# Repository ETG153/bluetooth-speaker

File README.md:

# Bluetooth-speaker
Wireless bluetooth speaker with high quality sound.

## Features
- Custom made sound card with an ESP32 and a high quality 24bit 192khz dac, Hi-Fi quality
- Completely wireless: battery charging and BMS included
- Amplifiers and crossover custom made for this product, design is power efficient
- Can support LDAC bluetooth codec for higher music bitrate (up to 990 kbps)

## Documentation
- Schematics can be found in the hardware folder
- Code is self explanatory, thus no documentation is needed
- PlatformIO: https://platformio.org/
- DAC datasheet: https://statics.cirrus.com/pubs/proDatasheet/CS4344-45-48_F2.pdf
- ESP32 datasheet: https://www.espressif.com/sites/default/files/documentation/esp32-wroom-32e_esp32-wroom-32ue_datasheet_en.pdf
- Bluetooth library used: https://github.com/pschatzmann/ESP32-A2DP

- Oamk documentation in its own folder

## Architecture

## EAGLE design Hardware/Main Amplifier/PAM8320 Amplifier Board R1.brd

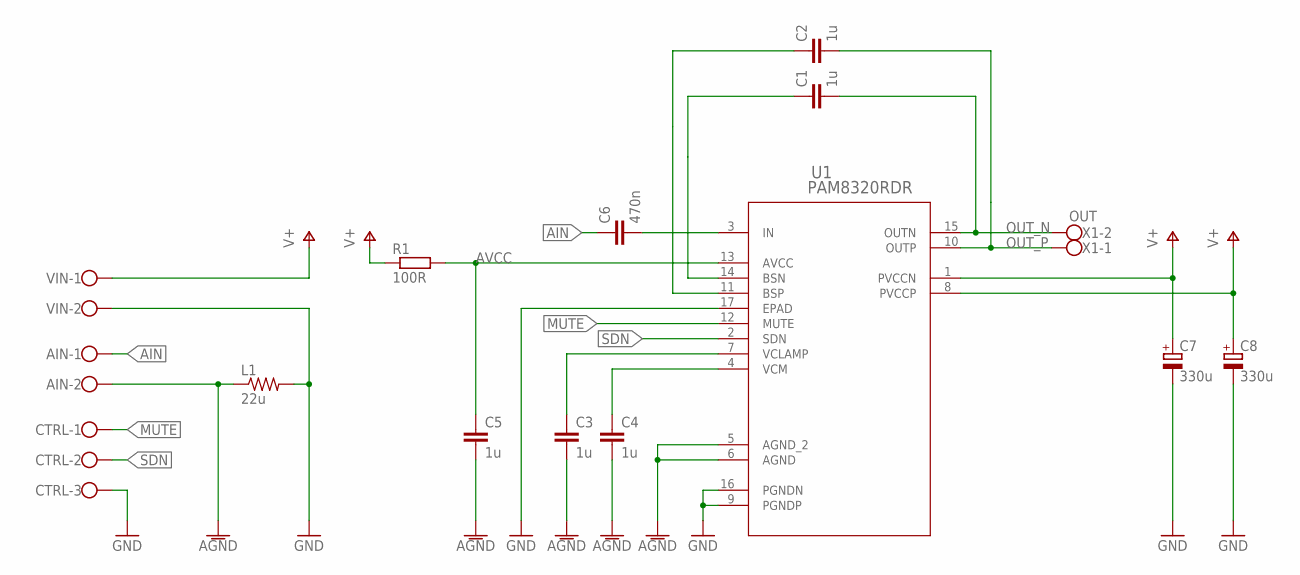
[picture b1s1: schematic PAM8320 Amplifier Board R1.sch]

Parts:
AIN: W237-102
C1, C2, C3, C4, C5: 1u; C1206
C6: 470n; C1206
C7, C8: 330u; E3,5-8
CTRL: W237-103
L1: 22u; R0805
R1: 100R; R0603
U1: PAM8320RDR; SO-16EP_3P9X9P9_DIO
VIN: W237-102
X1: OUT; W237-102

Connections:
AGND: AIN.2, C3.2, C4.2, C5.2, L1.1, U1.5 (AGND_2), U1.6 (AGND)
AIN: AIN.1, C6.1
AVCC: C5.1, R1.2, U1.13 (AVCC)
BSN: C1.1, U1.14 (BSN)
BSP: C2.1, U1.11 (BSP)
GND: C7.-, C8.-, CTRL.3, L1.2, U1.9 (PGNDP), U1.16 (PGNDN), U1.17 (EPAD), VIN.2
MUTE: CTRL.1, U1.12 (MUTE)
unnamed: C3.1, U1.7 (VCLAMP)
unnamed: C4.1, U1.4 (VCM)
unnamed: C6.2, U1.3 (IN)
OUT_N: C1.2, U1.15 (OUTN), X1.2
OUT_P: C2.2, U1.10 (OUTP), X1.1
SDN: CTRL.2, U1.2 (SDN)
V+: C7.+, C8.+, R1.1, U1.1 (PVCCN), U1.8 (PVCCP), VIN.1

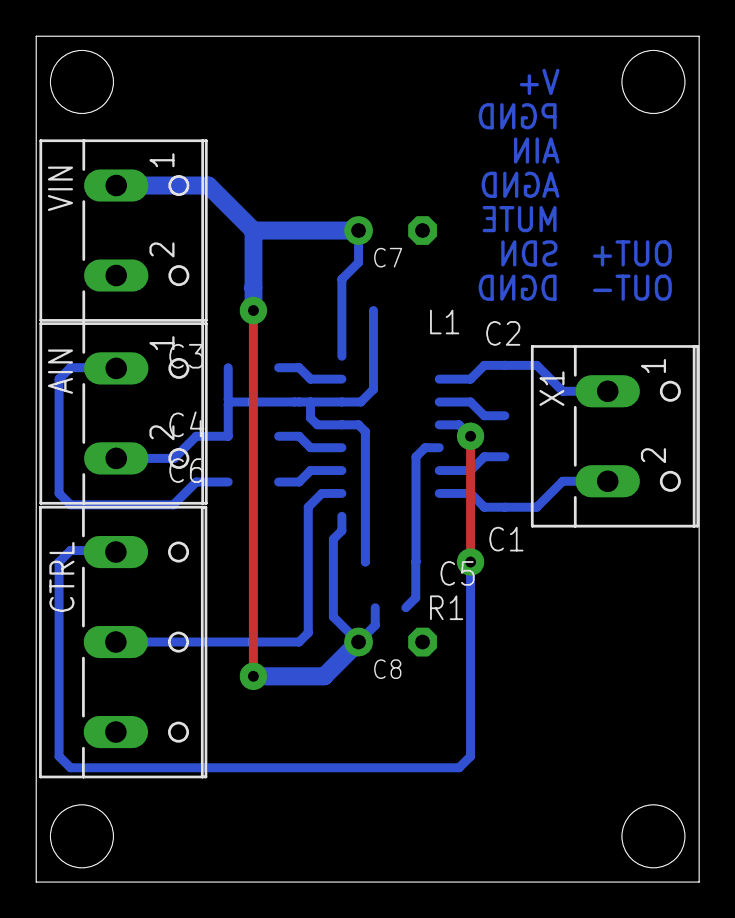
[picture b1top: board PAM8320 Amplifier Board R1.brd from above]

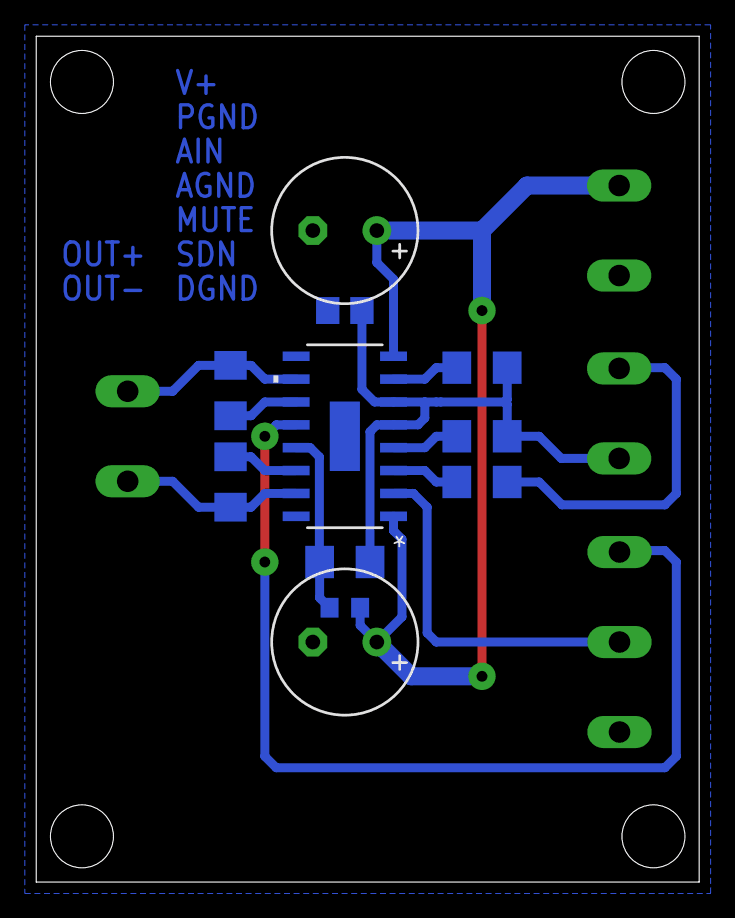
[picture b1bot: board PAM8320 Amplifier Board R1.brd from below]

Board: 2 copper layers, 36.8 x 47.0 mm, 15 parts (11 on the bottom side), 14 nets.

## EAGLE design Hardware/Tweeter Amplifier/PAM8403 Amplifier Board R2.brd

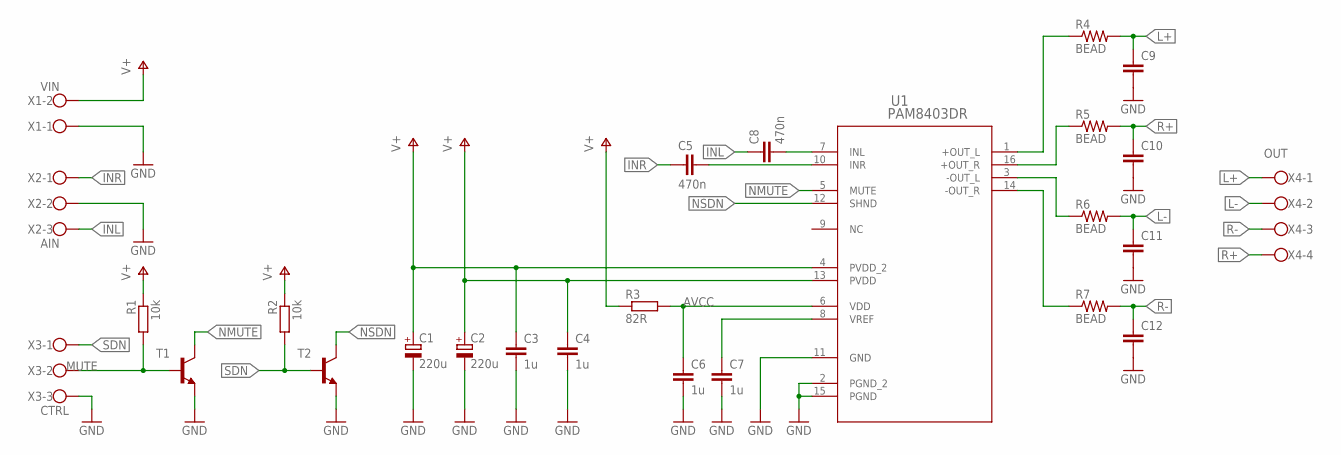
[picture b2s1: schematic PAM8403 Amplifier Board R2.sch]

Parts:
C1, C2: 220u; UD-10X10_NICHICON
C3, C4, C6, C7: 1u; C0805
C5, C8: 470n; C1206
C9, C10, C11, C12: C-EUC0603; C0603
R1, R2: 10k; R0603
R3: 82R; R1206
R4, R5, R6, R7: BEAD; R0805
T1, T2: MMBT3904LT1-NPN-SOT23-BEC; SOT23-BEC
U1: PAM8403DR; SOIC_8403DR_DIO
X1: VIN; W237-102
X2: AIN; W237-103
X3: CTRL; W237-103
X4: OUT; W237-4

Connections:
AVCC: C6.1, R3.2, U1.6 (VDD)
GND: C1.-, C2.-, C3.2, C4.2, C6.2, C7.2, C9.2, C10.2, C11.2, C12.2, T1.E, T2.E, U1.2 (PGND_2), U1.11 (GND), U1.15 (PGND), X1.1, X2.2, X3.3
INL: C8.1, X2.3
INR: C5.1, X2.1
L: C8.2, U1.7 (INL)
L+: C9.1, R4.2, X4.1
L-: C11.1, R6.2, X4.2
MUTE: R1.2, T1.B, X3.2
unnamed: R5.1, U1.16 (+OUT_R)
unnamed: R6.1, U1.3 (-OUT_L)
unnamed: R4.1, U1.1 (+OUT_L)
unnamed: R7.1, U1.14 (-OUT_R)
NMUTE: T1.C, U1.5 (MUTE)
NSDN: T2.C, U1.12 (SHND)
R: C5.2, U1.10 (INR)
R+: C10.1, R5.2, X4.4
R-: C12.1, R7.2, X4.3
SDN: R2.2, T2.B, X3.1
V+: C1.+, C2.+, C3.1, C4.1, R1.1, R2.1, R3.1, U1.4 (PVDD_2), U1.13 (PVDD), X1.2
VREF: C7.1, U1.8 (VREF)

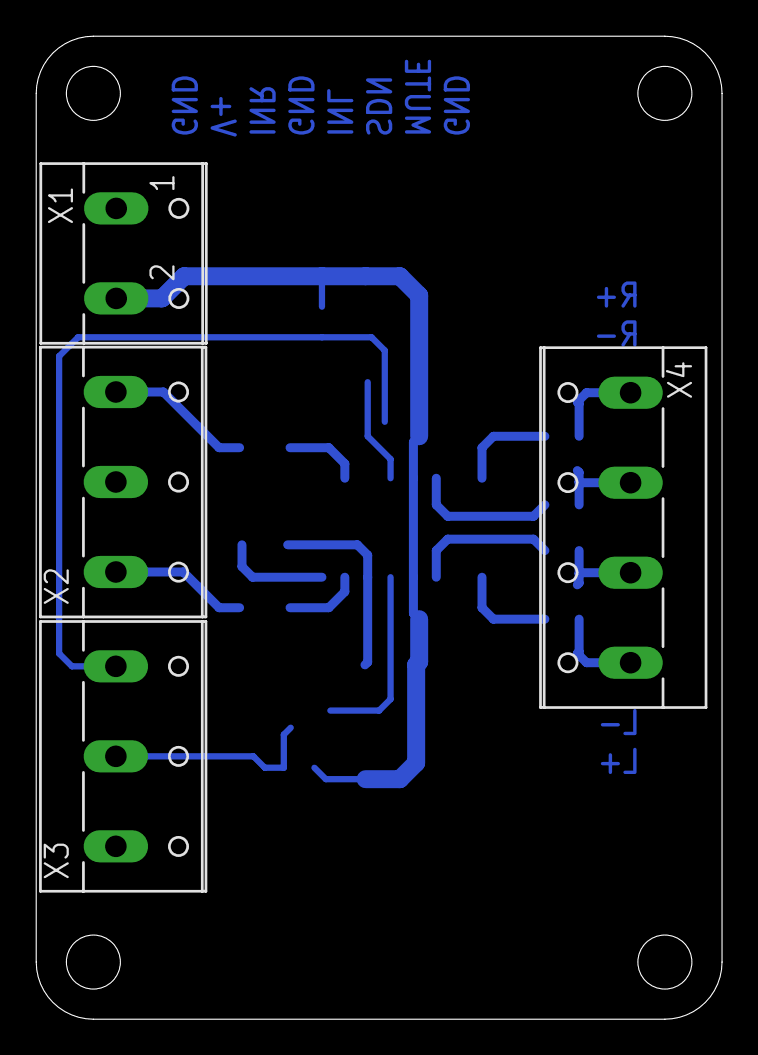
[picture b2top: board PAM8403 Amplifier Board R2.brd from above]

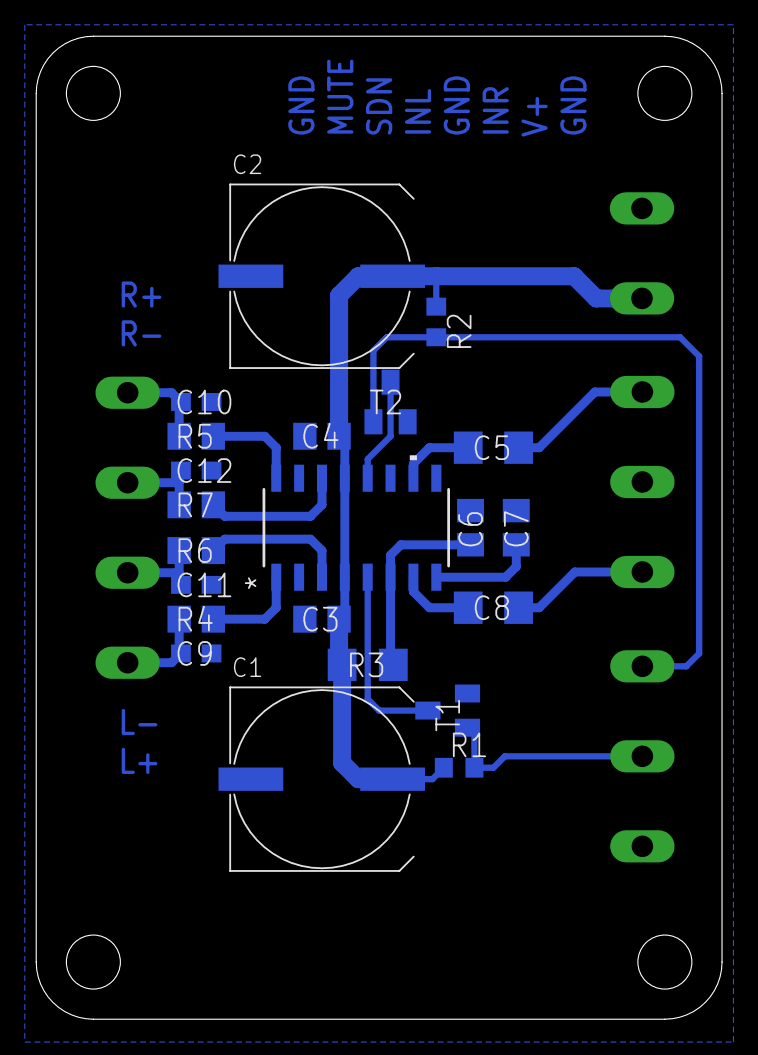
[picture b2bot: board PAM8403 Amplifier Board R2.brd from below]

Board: 2 copper layers, 38.1 x 54.6 mm, 26 parts (22 on the bottom side), 20 nets.

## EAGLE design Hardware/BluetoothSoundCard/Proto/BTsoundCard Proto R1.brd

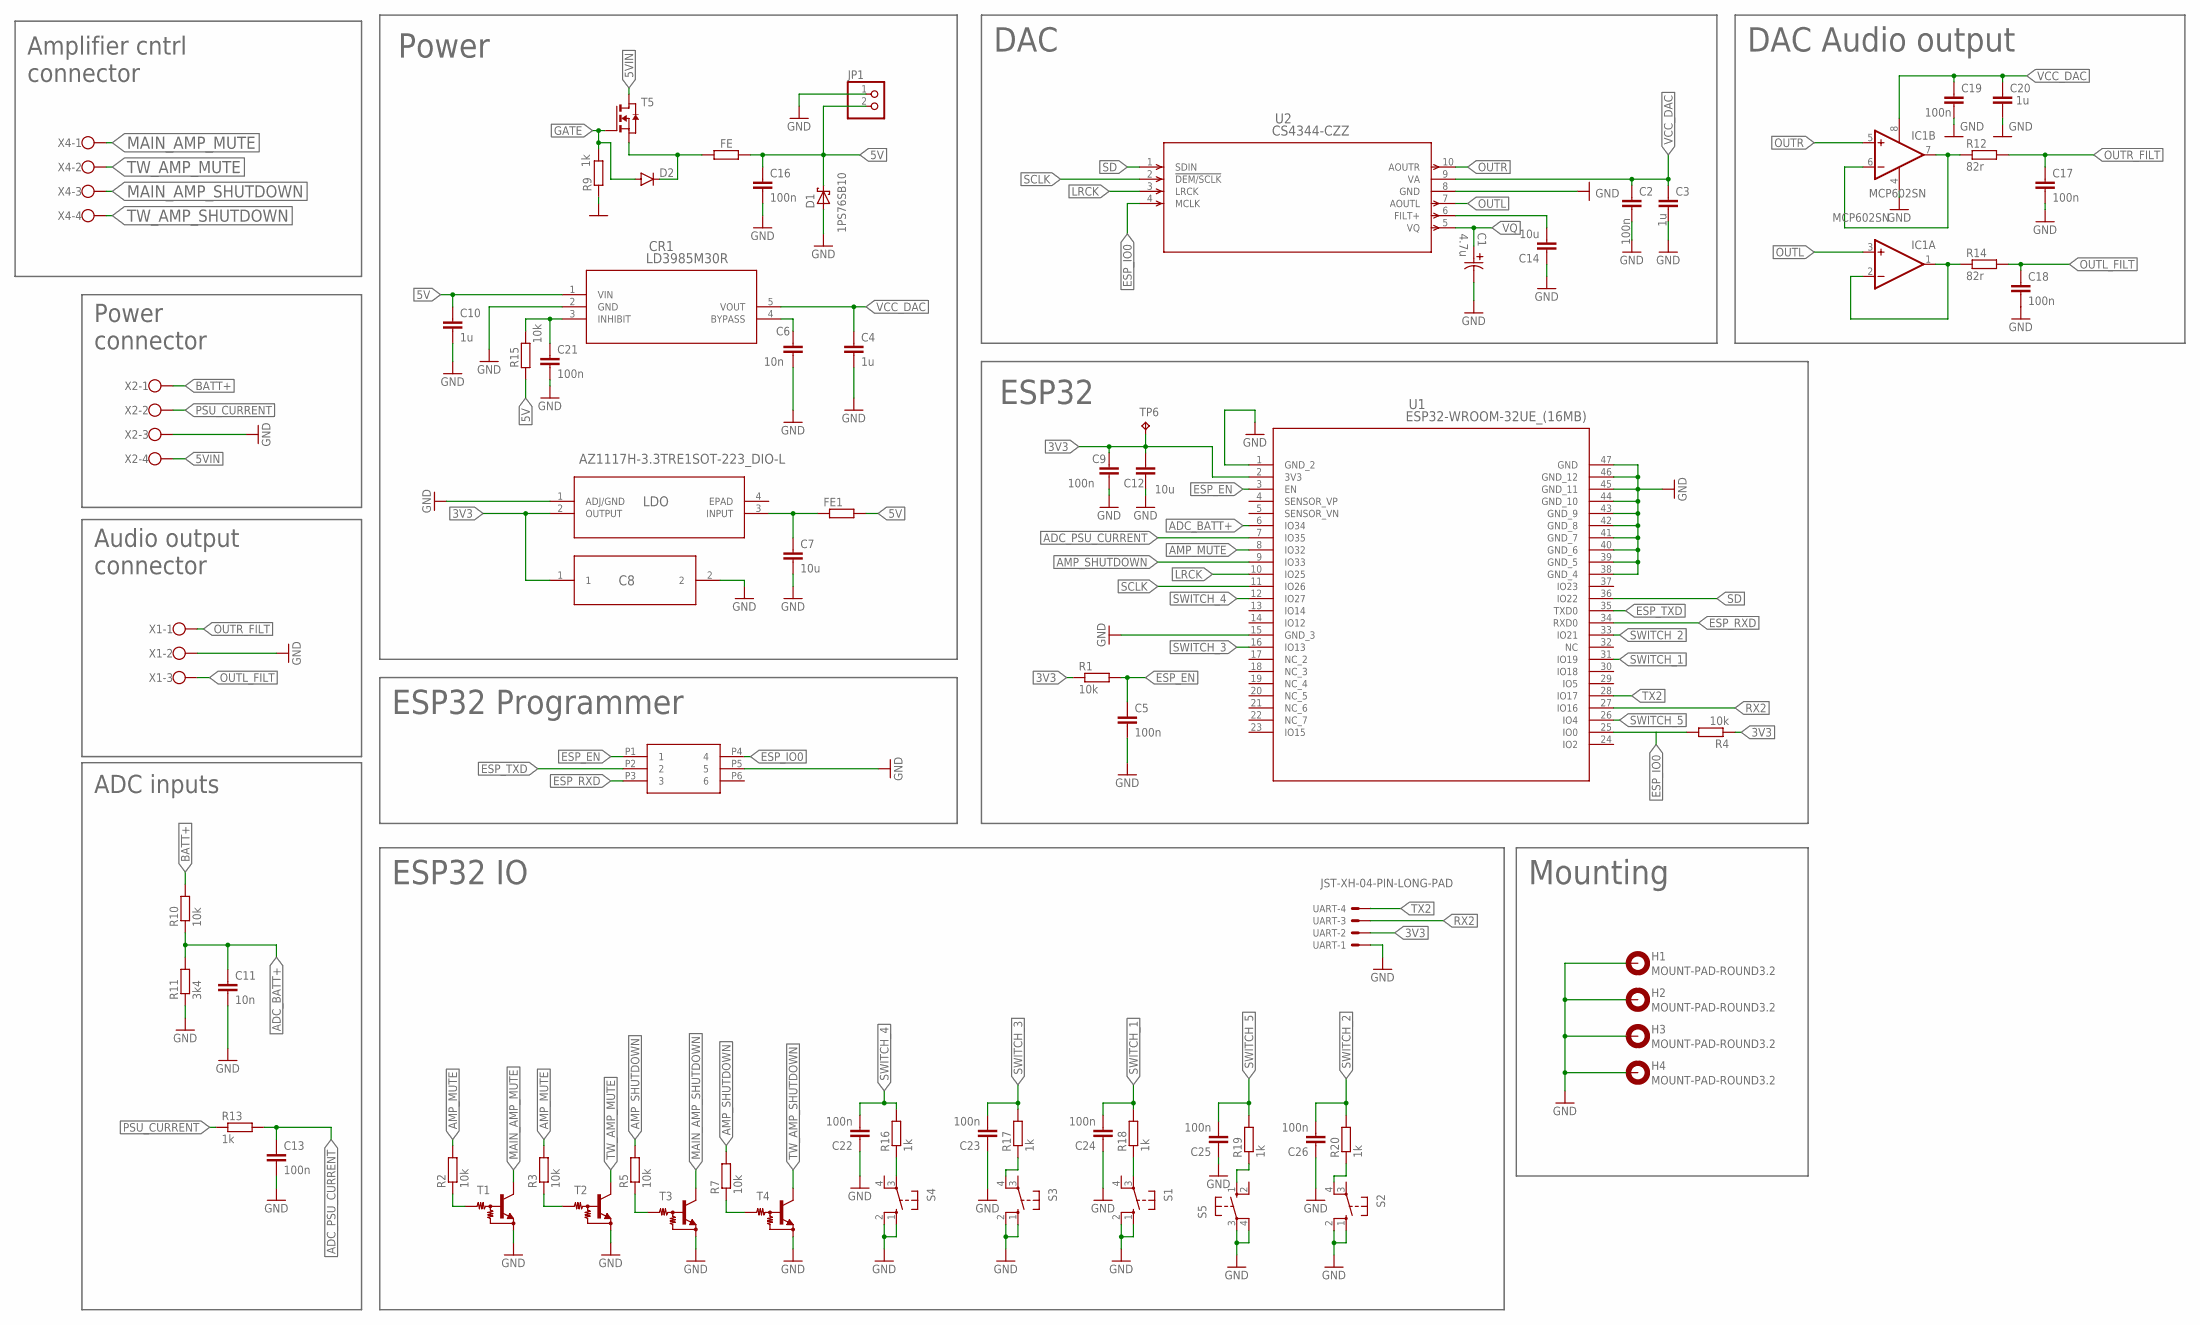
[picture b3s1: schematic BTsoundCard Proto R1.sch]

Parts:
C1: 4.7u; CAP_EEFK_B_PAN-M
C2, C5, C9, C13, C16, C17, C18, C19, C21, C22, C23, C24, C25, C26: 100n; C0603
C3, C4, C10, C20: 1u; C0603
C6, C11: 10n; C0603
C7, C12, C14: 10u; C0805
C8: TPSC336K010R0375; TPSC336K010R0375_AVX
CR1: LD3985M30R; SOT23-5L_STM
D1: 1PS76SB10; SOD323(F)
D2: 5.1V; MINIMELF
FE, FE1: R-EU_R0805; R0805
H1, H2, H3, H4: MOUNT-PAD-ROUND3.2; 3,2-PAD
IC1: MCP602SN; SO08
JP1: PINHD-1X2; 1X02
LDO: AZ1117H-3.3TRE1SOT-223_DIO-L; SOT-223_DIO-L
R1, R2, R3, R4, R5, R7, R15: 10k; R0603
R9: 1k; R1206
R10: 10k; R0805
R11: 3k4; R0603
R12, R14: 82r; R1206
R13, R16, R17, R18, R19, R20: 1k; R0603
S1, S2, S3, S4, S5: 10-XX; B3F-10XX
T1, T2, T3, T4: MUN2212T1-NPN_DRIVER-SC59-BEC; SC59-BEC
T5: NMOSSOT23; SOT-23
TP6: TPPAD1-13; P1-13
U1: ESP32-WROOM-32UE_(16MB); IC38_ESP32-WROOM-32UE_(16MB)_E
U2: CS4344-CZZ; CIR-TSSOP-10
U$3: 3X2; 2X3
UART: JST-XH-04-PIN-LONG-PAD; JST-XH-04-PACKAGE-LONG-PAD
X1: W237-103
X2, X4: W237-4

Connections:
3V3: C8.1, C9.1, C12.2, LDO.2 (OUTPUT), R1.1, R4.1, TP6.TP, U1.2 (3V3), UART.2
5V: C10.1, C16.1, CR1.1 (VIN), D1.1 (K), FE.2, FE1.2, JP1.2, R15.1
5VIN: T5.1 (D), X2.4
ADC_BATT+: C11.1, R10.1, R11.2, U1.6 (IO34)
ADC_PSU_CURRENT: C13.1, R13.2, U1.7 (IO35)
AMP_MUTE: R2.2, R3.2, U1.8 (IO32)
AMP_SHUTDOWN: R5.2, R7.2, U1.9 (IO33)
BATT+: R10.2, X2.1
ESP_EN: C5.1, R1.2, U1.3 (EN), U$3.P1 (1)
ESP_IO0: R4.2, U1.25 (IO0), U2.4 (MCLK), U$3.P4 (4)
ESP_RXD: U1.34 (RXD0), U$3.P3 (3)
ESP_TXD: U1.35 (TXD0), U$3.P2 (2)
GATE: D2.A, R9.2, T5.3 (G)
GND: C1.2, C2.2, C3.2, C4.2, C5.2, C6.2, C7.2, C8.2, C9.2, C10.2, C11.2, C12.1, C13.2, C14.1, C16.2, C17.2, C18.2, C19.2, C20.2, C21.2, C22.1, C23.1, C24.1, C25.1, C26.1, CR1.2 (GND), D1.2 (A), H1.B3,2, H2.B3,2, H3.B3,2, H4.B3,2, IC1.4 (V-), JP1.1, LDO.1 (ADJ/GND), R9.1, R11.1, S1.1 (S), S1.2 (S1), S2.1 (S), S2.2 (S1), S3.1 (S), S3.2 (S1), S4.1 (S), S4.2 (S1), S5.3, S5.4 (P1), T1.E, T2.E, T3.E, T4.E, U1.1 (GND_2), U1.15 (GND_3), U1.38 (GND_4), U1.39 (GND_5), U1.40 (GND_6), U1.41 (GND_7), U1.42 (GND_8), U1.43 (GND_9), U1.44 (GND_10), U1.45 (GND_11), U1.46 (GND_12), U1.47 (GND), U2.8 (GND), U$3.P5 (5), UART.1, X1.2, X2.3
LRCK: U1.10 (IO25), U2.3 (LRCK)
MAIN_AMP_MUTE: T1.C, X4.1
MAIN_AMP_SHUTDOWN: T3.C, X4.3
unnamed: IC1.6 (-IN), IC1.7 (OUT), R12.1
unnamed: R16.1, S4.3
unnamed: C6.1, CR1.4 (BYPASS)
unnamed: R17.1, S3.4 (P1)
unnamed: C14.2, U2.6 (FILT+)
unnamed: C7.1, FE1.1, LDO.3 (INPUT)
unnamed: R2.1, T1.B
unnamed: R3.1, T2.B
unnamed: R5.1, T3.B
unnamed: R7.1, T4.B
unnamed: R18.1, S1.3
unnamed: C21.1, CR1.3 (INHIBIT), R15.2
unnamed: R19.1, S5.1 (S)
unnamed: R20.1, S2.4 (P1)
unnamed: D2.C, FE.1, T5.2 (S)
unnamed: IC1.1 (OUT), IC1.2 (-IN), R14.1
OUTL: IC1.3 (+IN), U2.7 (AOUTL)
OUTL_FILT: C18.1, R14.2, X1.3
OUTR: IC1.5 (+IN), U2.10 (AOUTR)
OUTR_FILT: C17.1, R12.2, X1.1
PSU_CURRENT: R13.1, X2.2
RX2: U1.27 (IO16), UART.3
SCLK: U1.11 (IO26), U2.2 (!DEM/SCLK)
SD: U1.36 (IO22), U2.1 (SDIN)
SWITCH_1: C24.2, R18.2, U1.31 (IO19)
SWITCH_2: C26.2, R20.2, U1.33 (IO21)
SWITCH_3: C23.2, R17.2, U1.16 (IO13)
SWITCH_4: C22.2, R16.2, U1.12 (IO27)
SWITCH_5: C25.2, R19.2, U1.26 (IO4)
TW_AMP_MUTE: T2.C, X4.2
TW_AMP_SHUTDOWN: T4.C, X4.4
TX2: U1.28 (IO17), UART.4
VCC_DAC: C2.1, C3.1, C4.1, C19.1, C20.1, CR1.5 (VOUT), IC1.8 (V+), U2.9 (VA)
VQ: C1.1, U2.5 (VQ)

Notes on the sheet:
Power
DAC
ESP32
ESP32 Programmer
ESP32 IO
Mounting
Amplifier cntrl connector
Power connector
Audio output connector
ADC inputs
DAC Audio output

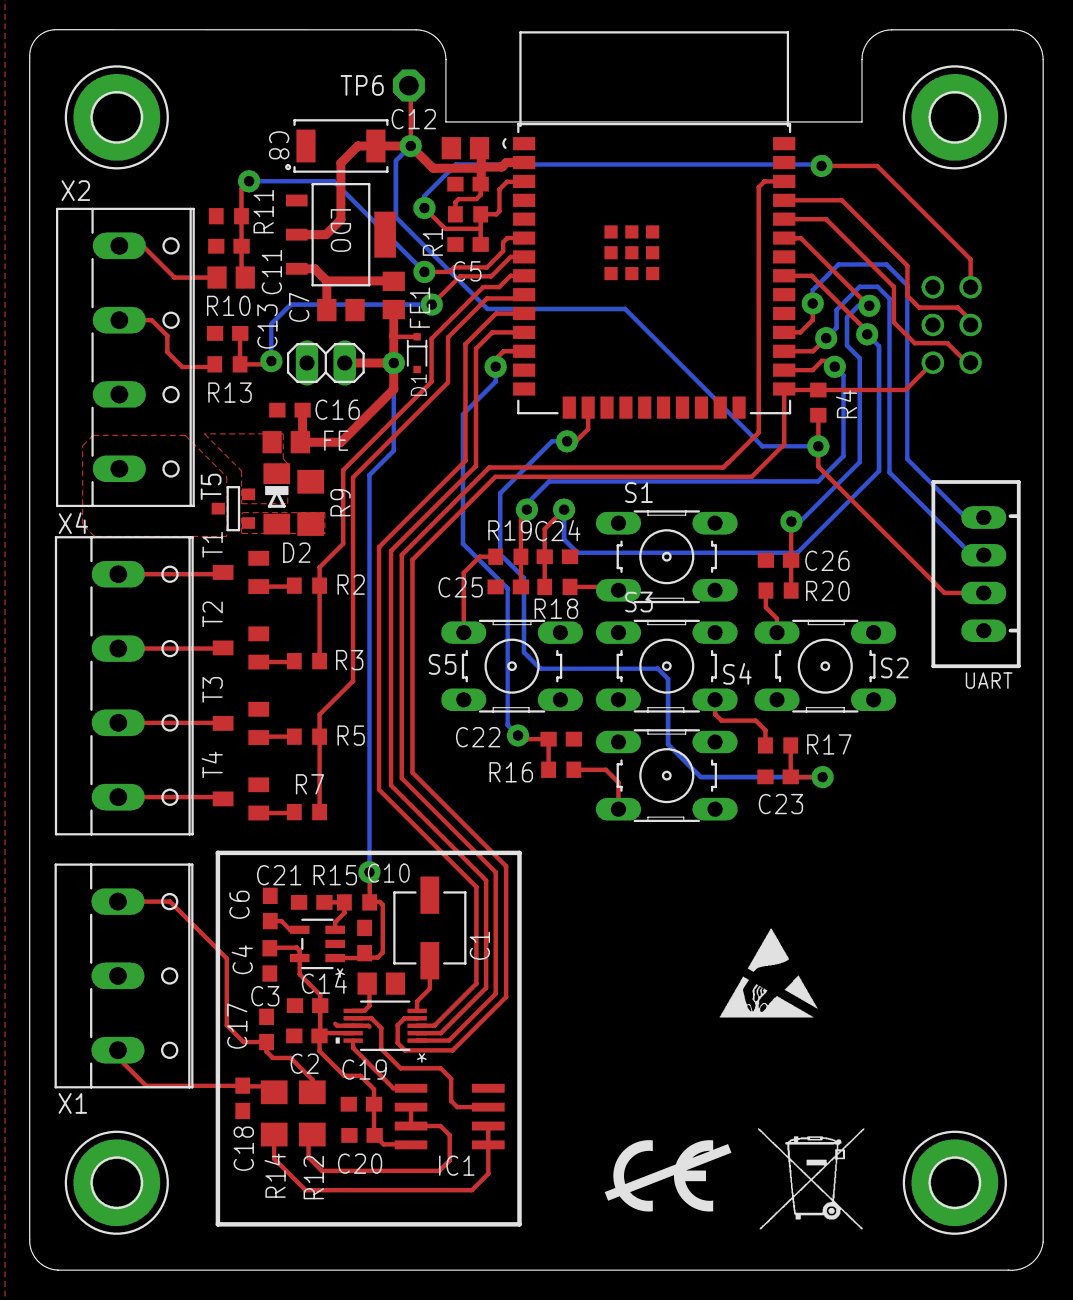
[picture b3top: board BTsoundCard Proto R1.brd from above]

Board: 2 copper layers, 68.2 x 83.5 mm, 73 parts (1 on the bottom side), 51 nets.

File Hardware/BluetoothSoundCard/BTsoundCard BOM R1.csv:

Qty;Value;Device;Package;Parts;Description
5;;10-XX;B3F-10XX;S1, S2, S3, S4, S5;OMRON SWITCH
1;;LEDCHIP-LED0603;CHIP-LED0603;LED2;LED
4;;MMBT3904 ;SOT23;T1, T2, T3, T4;NPN Transistor
1;;MMFTP3401;SOT-23;T5;MOS FET
1;;PINHD-1X2;1X02;JP1;PIN HEADER
2;;R-EU_R0805;R0805;FE, FE1;FERRITE BEAD
1;;W237-103;W237-103;X1;WAGO SCREW CLAMP
2;;W237-4;W237-4;X2, X4;WAGO SCREW CLAMP
14;100n;C-EUC0603;C0603;C2, C5, C9, C13, C16, C17, C18, C19, C21, C22, C23, C24, C25, C26;CAPACITOR, European symbol
7;10k;R-EU_R0603;R0603;R1, R2, R3, R4, R5, R7, R15;RESISTOR, European symbol
1;10k;R-EU_R0805;R0805;R10;RESISTOR, European symbol
2;10n;C-EUC0603;C0603;C6, C11;CAPACITOR, European symbol
3;10u;C-EUC0805;C0805;C7, C12, C14;CAPACITOR, European symbol
1;1PS76SB10;1PS76SB10;SOD323(F);D1;TVS DIODE
7;1k;R-EU_R0603;R0603;R8, R13, R16, R17, R18, R19, R20;RESISTOR, European symbol
1;1k;R-EU_R1206;R1206;R9;RESISTOR, European symbol
4;1u;C-EUC0603;C0603;C3, C4, C10, C20;CAPACITOR, European symbol
1;3X2;3X2;2X3;U$3;
1;3k4;R-EU_R0603;R0603;R11;RESISTOR, European symbol
1;4.7u;EEEFK1H4R7RCAP_EEFK_B_PAN-M;CAP_EEFK_B_PAN-M;C1;
1;5.1V;DIODE-MINIMELF;MINIMELF;D2;ZENER DIODE
2;82r;R-EU_R1206;R1206;R12, R14;RESISTOR, European symbol
1;AZ1117H-3.3TRE1SOT-223_DIO-L;AZ1117H-3.3TRE1SOT-223_DIO-L;SOT-223_DIO-L;LDO;
1;CS4344-CZZ;CS4344-CZZ;CIR-TSSOP-10;U2;
1;ESP32-WROOM-32UE_(16MB);ESP32-WROOM-32UE_(16MB);IC38_ESP32-WROOM-32UE_(16MB)_E;U1;
1;JST-XH-04-PIN-LONG-PAD;JST-XH-04-PIN-LONG-PAD;JST-XH-04-PACKAGE-LONG-PAD;UART;JST XH Connector 2 Pin
1;LD3985M30R;LD3985M30R;SOT23-5L_STM;CR1;
1;MCP602SN;MCP602SN;SO08;IC1;Single Op Amp 2.7V to 6.0V Single Supply CMOS
4;MOUNT-PAD-ROUND3.2;MOUNT-PAD-ROUND3.2;3,2-PAD;H1, H2, H3, H4;MOUNTING PAD, round
1;TPPAD1-13;TPPAD1-13;P1-13;TP6;Test pad
1;TPSC336K010R0375;TPSC336K010R0375;TPSC336K010R0375_AVX;C8;33uF low ESR tantalum capacitor

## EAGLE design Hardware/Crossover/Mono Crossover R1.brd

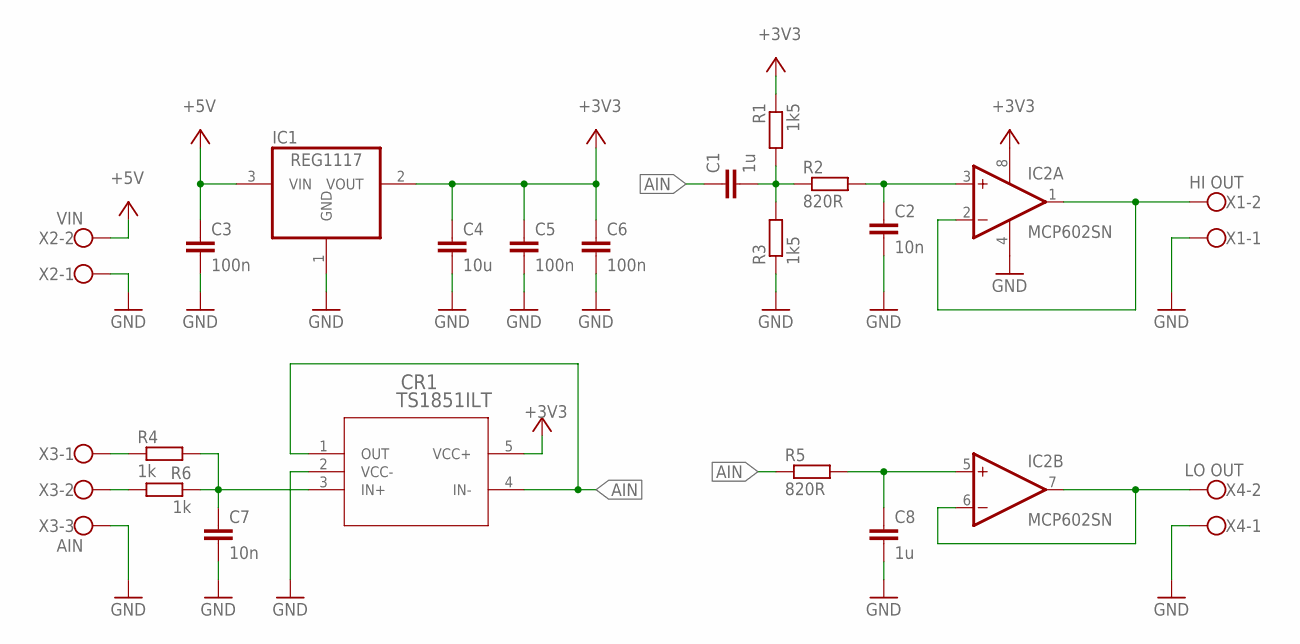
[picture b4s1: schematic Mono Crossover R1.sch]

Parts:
C1, C8: 1u; C0805
C2, C7: 10n; C0603
C3, C5, C6: 100n; C0603
C4: 10u; C1206
CR1: TS1851ILT; SOT23-5L_STM
IC1: REG1117; SOT223
IC2: MCP602SN; SO08
R1, R3: 1k5; R0805
R2, R5: 820R; R1206
R4, R6: 1k; R0603
X1: HI OUT; W237-102
X2: VIN; W237-102
X3: AIN; W237-103
X4: LO OUT; W237-102

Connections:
+3V3: C4.1, C5.1, C6.1, CR1.5 (VCC+), IC1.2 (VOUT), IC2.8 (V+), R1.1
+5V: C3.1, IC1.3 (VIN), X2.2
AIN: C1.1, CR1.1 (OUT), CR1.4 (IN-), R5.1
GND: C2.2, C3.2, C4.2, C5.2, C6.2, C7.2, C8.2, CR1.2 (VCC-), IC1.1 (GND), IC2.4 (V-), R3.1, X1.1, X2.1, X3.3, X4.1
HI_OUT: IC2.1 (OUT), IC2.2 (-IN), X1.2
LO_OUT: IC2.6 (-IN), IC2.7 (OUT), X4.2
unnamed: R4.1, X3.1
unnamed: R6.2, X3.2
unnamed: C2.1, IC2.3 (+IN), R2.2
unnamed: C1.2, R1.2, R2.1, R3.2
unnamed: C8.1, IC2.5 (+IN), R5.2
unnamed: C7.1, CR1.3 (IN+), R4.2, R6.1

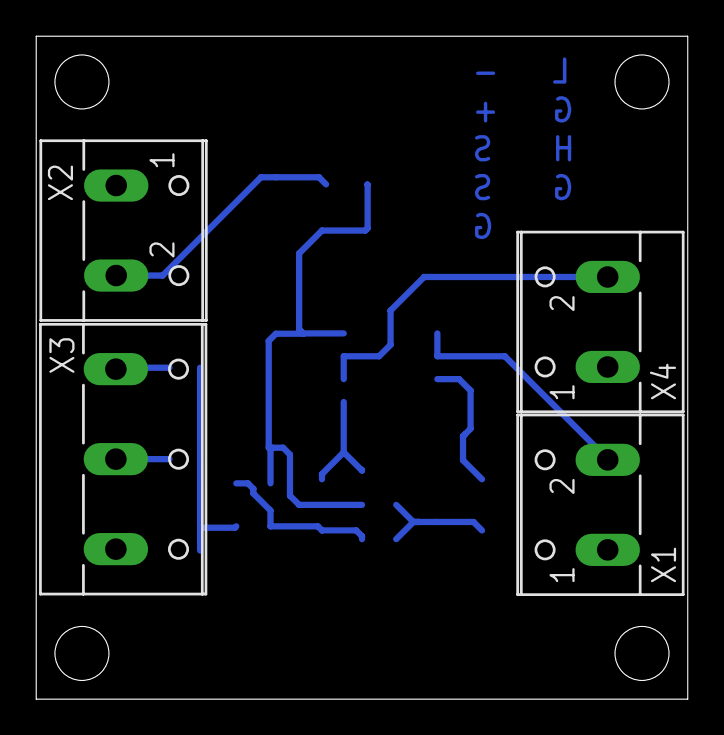
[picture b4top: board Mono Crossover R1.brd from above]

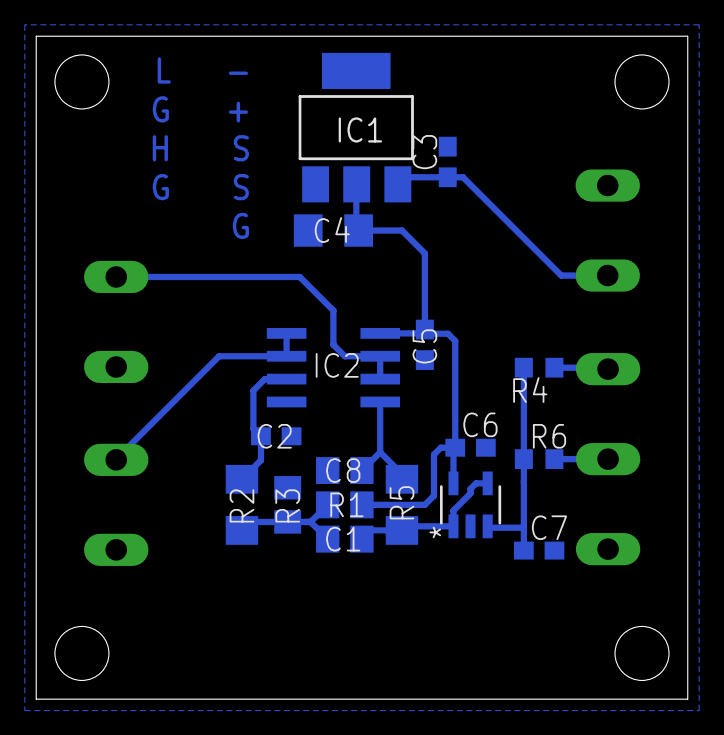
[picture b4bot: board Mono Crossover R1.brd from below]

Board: 2 copper layers, 36.2 x 36.8 mm, 21 parts (17 on the bottom side), 12 nets.

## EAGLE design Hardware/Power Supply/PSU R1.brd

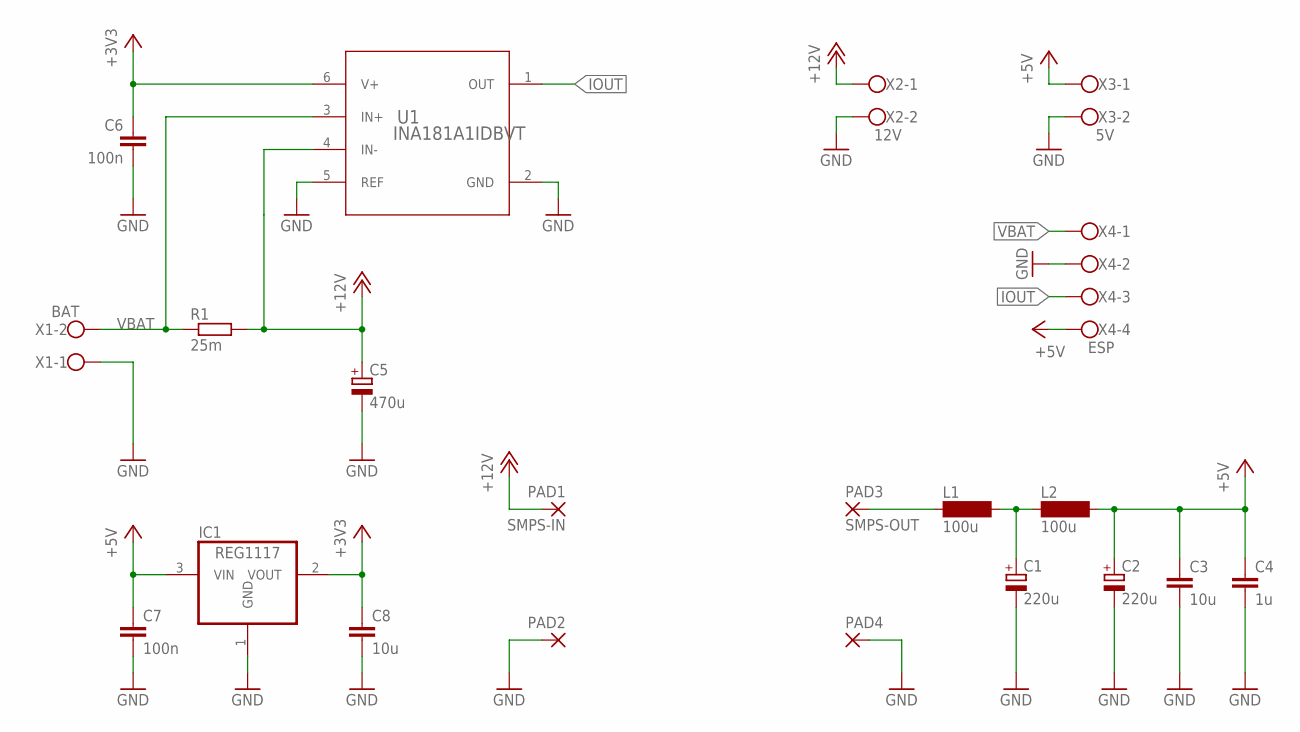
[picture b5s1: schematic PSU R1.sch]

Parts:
C1, C2: 220u; E2,5-6
C3, C8: 10u; C1206
C4: 1u; C0805
C5: 470u; E5-10,5
C6, C7: 100n; C0603
IC1: REG1117; SOT223
L1, L2: 100u; SD8
PAD1: SMPS-IN; 1,6/0,9
PAD2, PAD4: 1,6/0,9
PAD3: SMPS-OUT; 1,6/0,9
R1: 25m; R2512
U1: INA181A1IDBVT; DBV0006A_N
X1: BAT; W237-102
X2: 12V; W237-102
X3: 5V; W237-102
X4: ESP; W237-4

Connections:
+3V3: C6.1, C8.1, IC1.2 (VOUT), U1.6 (V+)
+5V: C2.+, C3.1, C4.1, C7.1, IC1.3 (VIN), L2.2, X3.1, X4.4
+12V: C5.+, PAD1.1, R1.2, U1.4 (IN-), X2.1
GND: C1.-, C2.-, C3.2, C4.2, C5.-, C6.2, C7.2, C8.2, IC1.1 (GND), PAD2.1, PAD4.1, U1.2 (GND), U1.5 (REF), X1.1, X2.2, X3.2, X4.2
IOUT: U1.1 (OUT), X4.3
unnamed: L1.1, PAD3.1
unnamed: C1.+, L1.2, L2.1
VBAT: R1.1, U1.3 (IN+), X1.2, X4.1

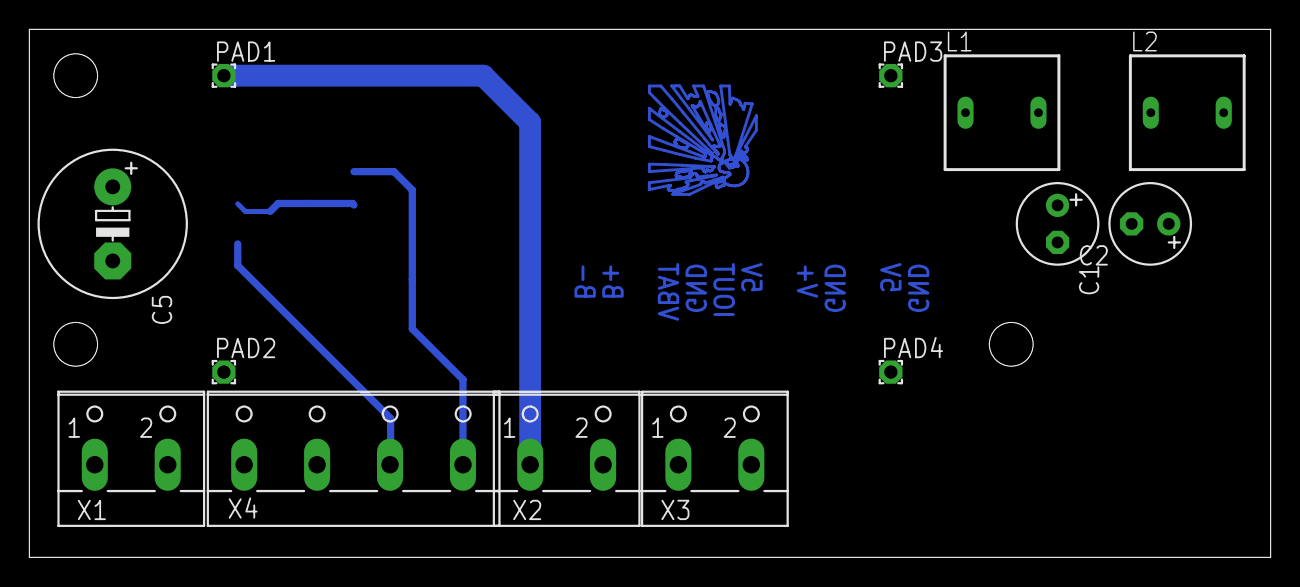
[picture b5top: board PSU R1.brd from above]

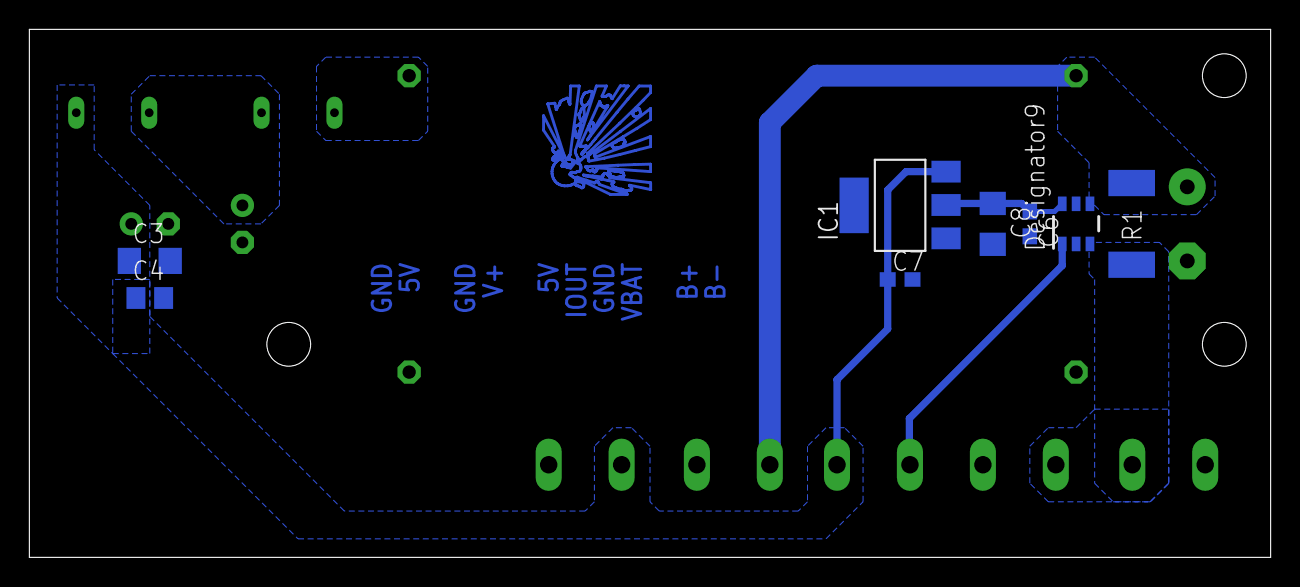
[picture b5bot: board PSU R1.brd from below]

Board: 2 copper layers, 85.1 x 36.2 mm, 21 parts (8 on the bottom side), 8 nets.

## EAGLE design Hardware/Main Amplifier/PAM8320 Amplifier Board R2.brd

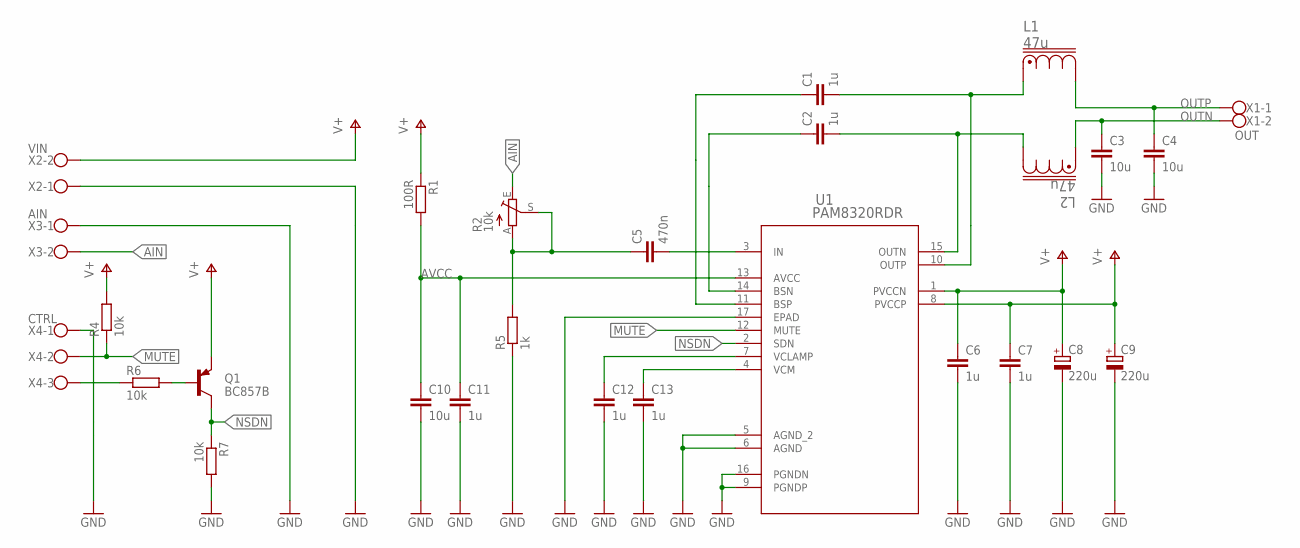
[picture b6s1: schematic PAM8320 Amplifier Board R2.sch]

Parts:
C1, C2, C6, C7, C11, C12, C13: 1u; C0805
C3, C4, C10: 10u; C1206
C5: 470n; C1206
C8, C9: 220u; UD-10X10_NICHICON
L1, L2: 47u; DR127
Q1: BC857B; SOT23-BEC
R1: 100R; R0603
R2: 10k; RJ9W
R4, R6, R7: 10k; R0603
R5: 1k; R0603
U1: PAM8320RDR; SO-16EP_3P9X9P9_DIO
X1: OUT; W237-102
X2: VIN; W237-102
X3: AIN; W237-102
X4: CTRL; W237-103

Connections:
AIN: R2.E, X3.2
AVCC: C10.1, C11.1, R1.2, U1.13 (AVCC)
BSN: C2.1, U1.14 (BSN)
BSP: C1.1, U1.11 (BSP)
GND: C3.2, C4.2, C6.2, C7.2, C8.-, C9.-, C10.2, C11.2, C12.2, C13.2, R5.1, R7.2, U1.5 (AGND_2), U1.6 (AGND), U1.9 (PGNDP), U1.16 (PGNDN), U1.17 (EPAD), X2.1, X3.1, X4.1
MUTE: R4.1, U1.12 (MUTE), X4.2
unnamed: Q1.B, R6.2
unnamed: C12.1, U1.7 (VCLAMP)
unnamed: C13.1, U1.4 (VCM)
unnamed: C5.1, R2.A, R2.S, R5.2
unnamed: C5.2, U1.3 (IN)
unnamed: R6.1, X4.3
NSDN: Q1.C, R7.1, U1.2 (SDN)
OUTN: C3.1, L2.1, X1.2
OUTP: C4.1, L1.2, X1.1
OUT_N: C2.2, L2.2, U1.15 (OUTN)
OUT_P: C1.2, L1.1, U1.10 (OUTP)
V+: C6.1, C7.1, C8.+, C9.+, Q1.E, R1.1, R4.2, U1.1 (PVCCN), U1.8 (PVCCP), X2.2

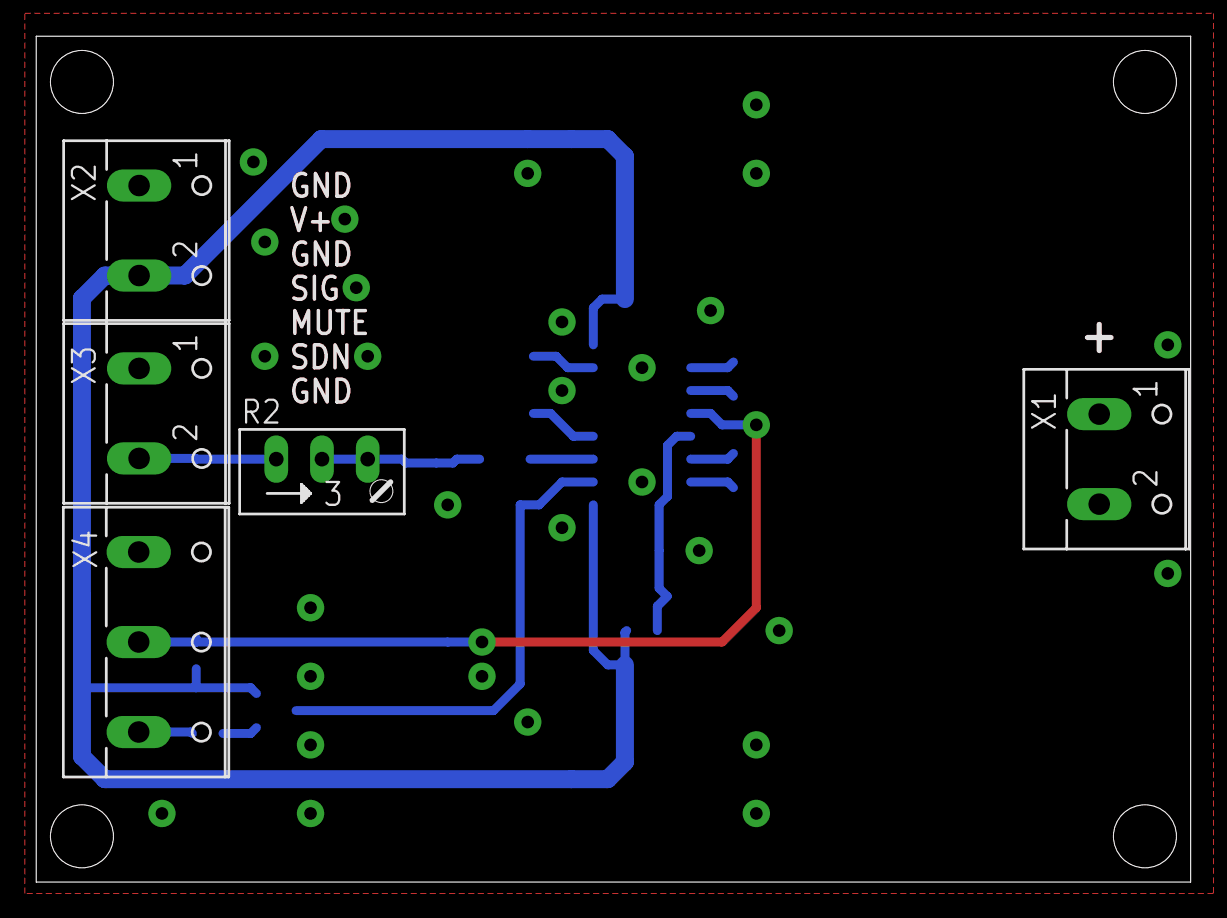
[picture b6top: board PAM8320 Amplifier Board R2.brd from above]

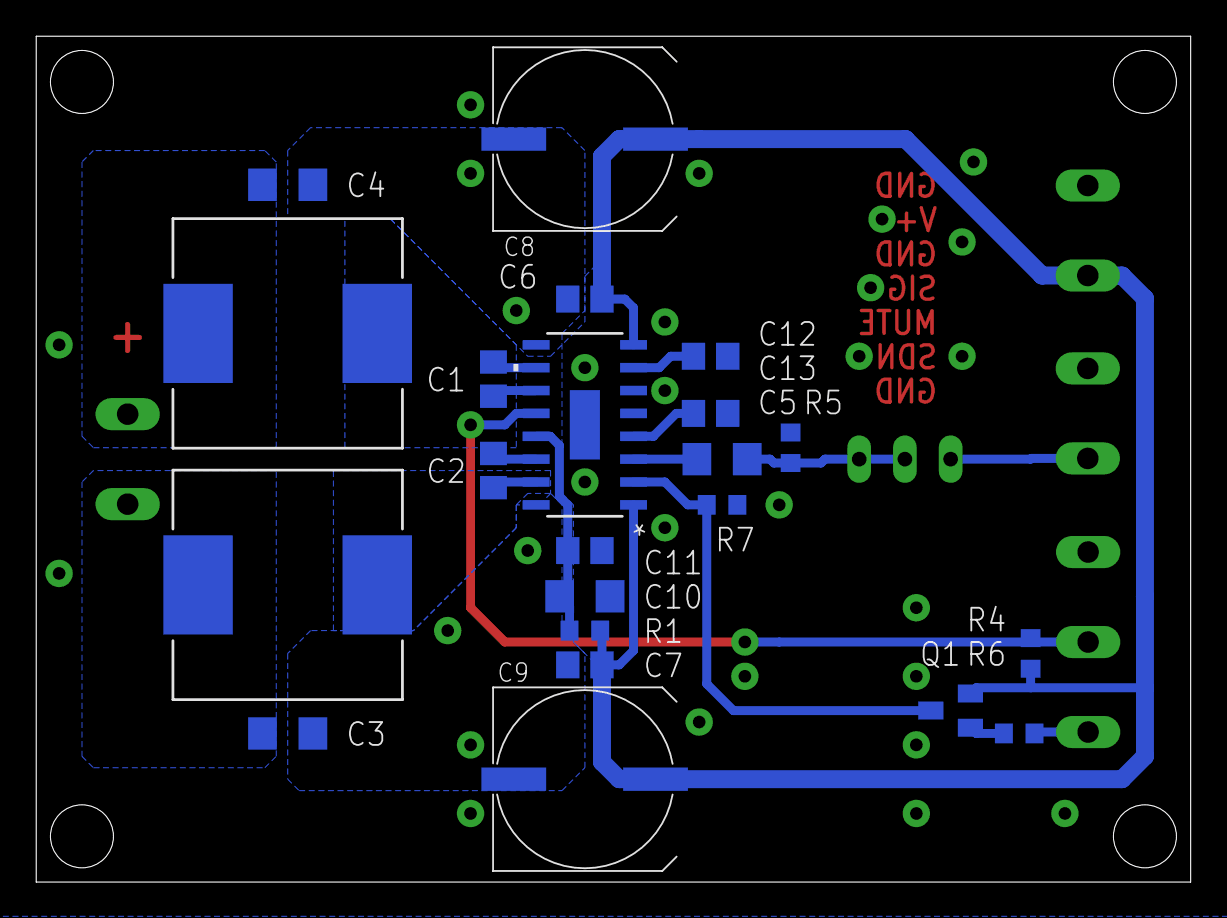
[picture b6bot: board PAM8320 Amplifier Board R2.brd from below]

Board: 2 copper layers, 64.1 x 47.0 mm, 27 parts (22 on the bottom side), 18 nets.

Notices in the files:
parts and their libraries:
COPYRIGHT: Copyright (C) 2018 Accelerated Designs. All rights reserved
COPYRIGHT: Copyright (C) 2022 Ultra Librarian. All rights reserved.
COPYRIGHT: Copyright (C) 2023 Ultra Librarian. All rights reserved.
